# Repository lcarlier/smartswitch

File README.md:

# My Smart switch
This project implements a smart switch based on Atmega328 that has the following requirements:

- Must fit into a wall switch case box
- Must be as less invasive as possible. Which means I did not want to change anything in my electrical installation, e.g to change my regular switches to push button switches.
- The physical switch must be available and functional (you don't want your wife to be angry with you because she can't open a light without her cellphone ;) )
- Even if my smart switch is blocked or dead, the physical switch must still work

Here is the way the Smart switch is to be connected with the 3 way physical switch

For the full description of this project, please consult [this post on my website](https://www.laurentcarlier.com/2018/04/My-smart-switch-project.html).

I also have 2 videos. The first one showing the project operating a small LED without any problem. The second video shows the
project operating a regular light bulb, but with problems.

- https://youtu.be/OeRLf1SrVcU
- https://youtu.be/o9J_xXDBoP8

On the second video, the power supply (HPK-PM01) was not in used yet. The power is provided by the 5V serial connector.

I do not have any idea yet what the problem is. Do not hesitate to contact me if you have a clue of what the problem can be. I'm most likely missing something related to high voltages and noise.

Enjoy!

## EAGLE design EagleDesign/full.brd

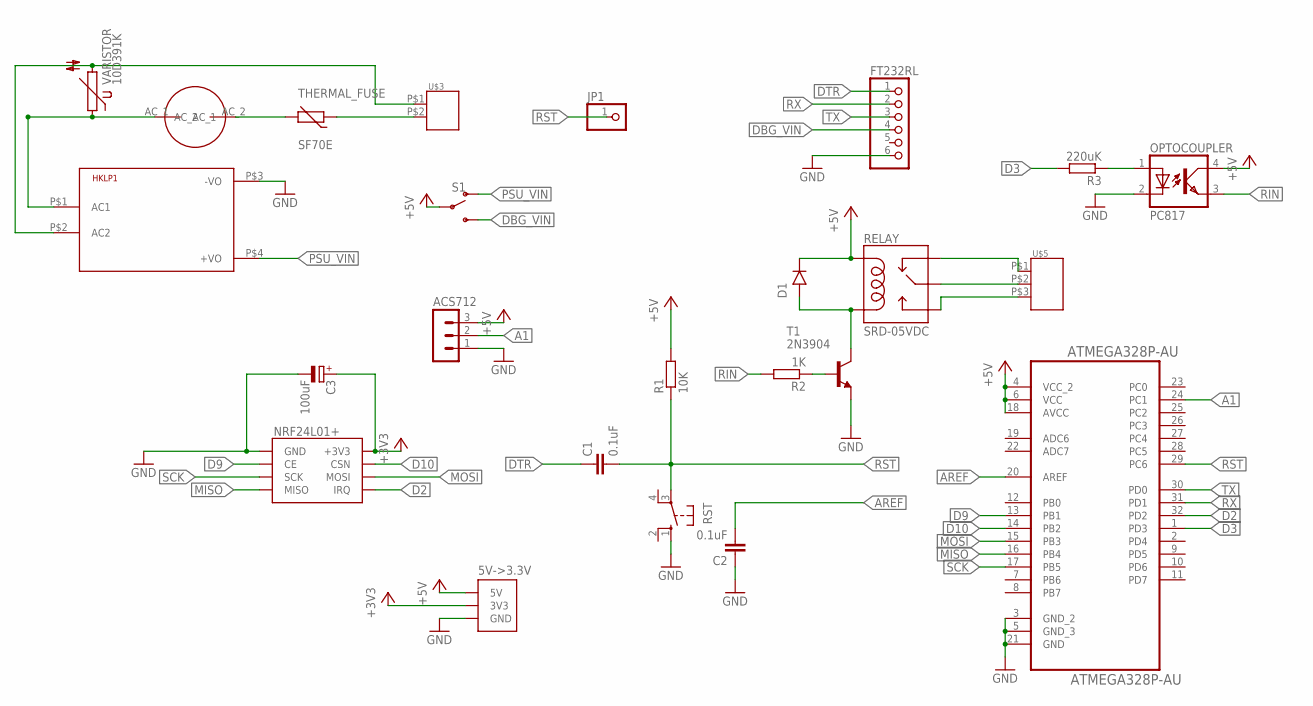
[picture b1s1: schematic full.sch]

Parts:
5V->3.3V: AMS1117_VERT
ACS712: MA03-1
ATMEGA328P-AU: ATMEGA328P-AU; QFP80P900X900X120-32N
C1, C2: 0.1uF; C050-030X075
C3: 100uF; E2,5-6
D1: 1N4001; DO41-10
FT232RL: PINHD-1X6; 1X06
FUSE: R3-24
HKLP1: HKLPM01
JP1: PINHD-1X1; 1X01
NRF24L01+: RADIO_NRF24L1; NRF24L1
OPTOCOUPLER: PC817; DIL04
R1: 10K; 0204/5
R2: 1K; 0204/5
R3: 220uK; 0204/5
RELAY: SRD-05VDC; SRD-05VDC-SL-C
RST: 10-XX; B3F-10XX
S1: SWITCH-SPDT-PTH-11.6X4.0MM; SWITCH_SPDT_PTH_11.6X4.0MM
T1: 2N3904; TO92
THERMAL_FUSE: SF70E; R-7,5
U$3: CONNECTOR_2SCREW; SCREW_2
U$5: CONNECTOR_3SCREW; SCREW_3
VARISTOR: 10D391K; S10K385

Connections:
+3V3: 5V->3.3V.3V3, C3.+, NRF24L01+.+3V3
+5V: 5V->3.3V.5V, ACS712.3, ATMEGA328P-AU.4 (VCC_2), ATMEGA328P-AU.6 (VCC), ATMEGA328P-AU.18 (AVCC), D1.C (CATHODE), OPTOCOUPLER.4 (COL), R1.2, RELAY.COIL1, S1.2
A1: ACS712.2, ATMEGA328P-AU.24 (PC1)
AC1_F: FUSE.AC_1, HKLP1.P$1 (AC1), VARISTOR.1
AC2: HKLP1.P$2 (AC2), U$3.P$1 (1), VARISTOR.2
AREF: ATMEGA328P-AU.20 (AREF), C2.2
D2: ATMEGA328P-AU.32 (PD2), NRF24L01+.IRQ
D3: ATMEGA328P-AU.1 (PD3), R3.2
D9: ATMEGA328P-AU.13 (PB1), NRF24L01+.CE
D10: ATMEGA328P-AU.14 (PB2), NRF24L01+.CSN
DBG_VIN: FT232RL.4, S1.3 (S)
DTR: C1.1, FT232RL.1
FU_IN: FUSE.AC_2, THERMAL_FUSE.2
GND: 5V->3.3V.GND, ACS712.1, ATMEGA328P-AU.3 (GND_2), ATMEGA328P-AU.5 (GND_3), ATMEGA328P-AU.21 (GND), C2.1, C3.-, FT232RL.6, HKLP1.P$3 (-VO), NRF24L01+.GND, OPTOCOUPLER.2 (C), RST.1 (S), T1.3 (E)
MISO: ATMEGA328P-AU.16 (PB4), NRF24L01+.MISO
MOSI: ATMEGA328P-AU.15 (PB3), NRF24L01+.MOSI
OPTO_IN: OPTOCOUPLER.1 (A), R3.1
PSU_VIN: HKLP1.P$4 (+VO), S1.1 (O)
RIN: OPTOCOUPLER.3 (EMIT), R2.2
RST: ATMEGA328P-AU.29 (PC6), C1.2, JP1.1, R1.1, RST.3
RX: ATMEGA328P-AU.31 (PD1), FT232RL.2
R_CENTER: RELAY.SWCOMMON, U$5.P$2 (2)
R_IN: D1.A (ANODE), RELAY.COIL0, T1.1 (C)
R_LEFT: RELAY.SWOPEN, U$5.P$3 (3)
R_RIGHT: RELAY.SWCLOSED (SWCLOSE), U$5.P$1 (1)
SCK: ATMEGA328P-AU.17 (PB5), NRF24L01+.SCK
TR_IN: THERMAL_FUSE.1, U$3.P$2 (2)
TX: ATMEGA328P-AU.30 (PD0), FT232RL.3
T_IN: R2.1, T1.2 (B)

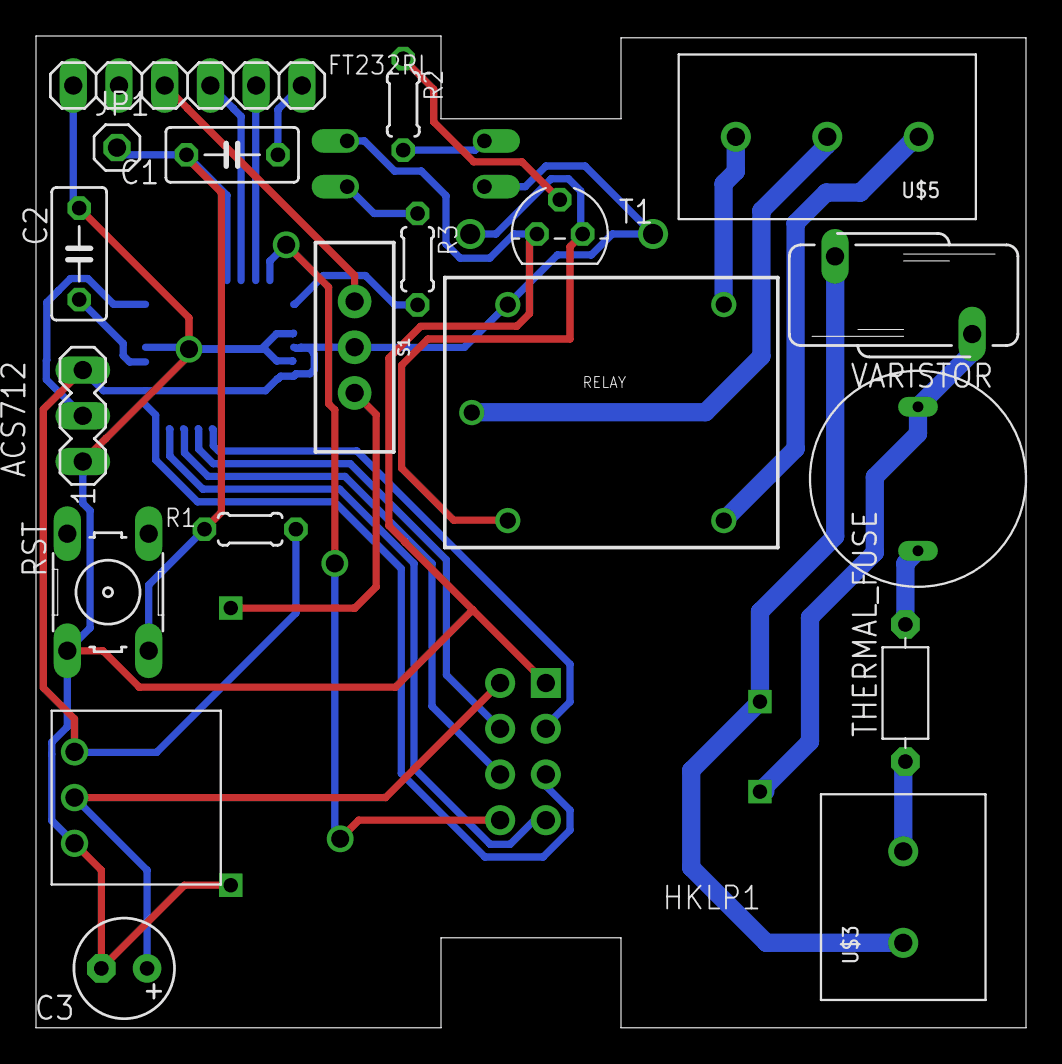
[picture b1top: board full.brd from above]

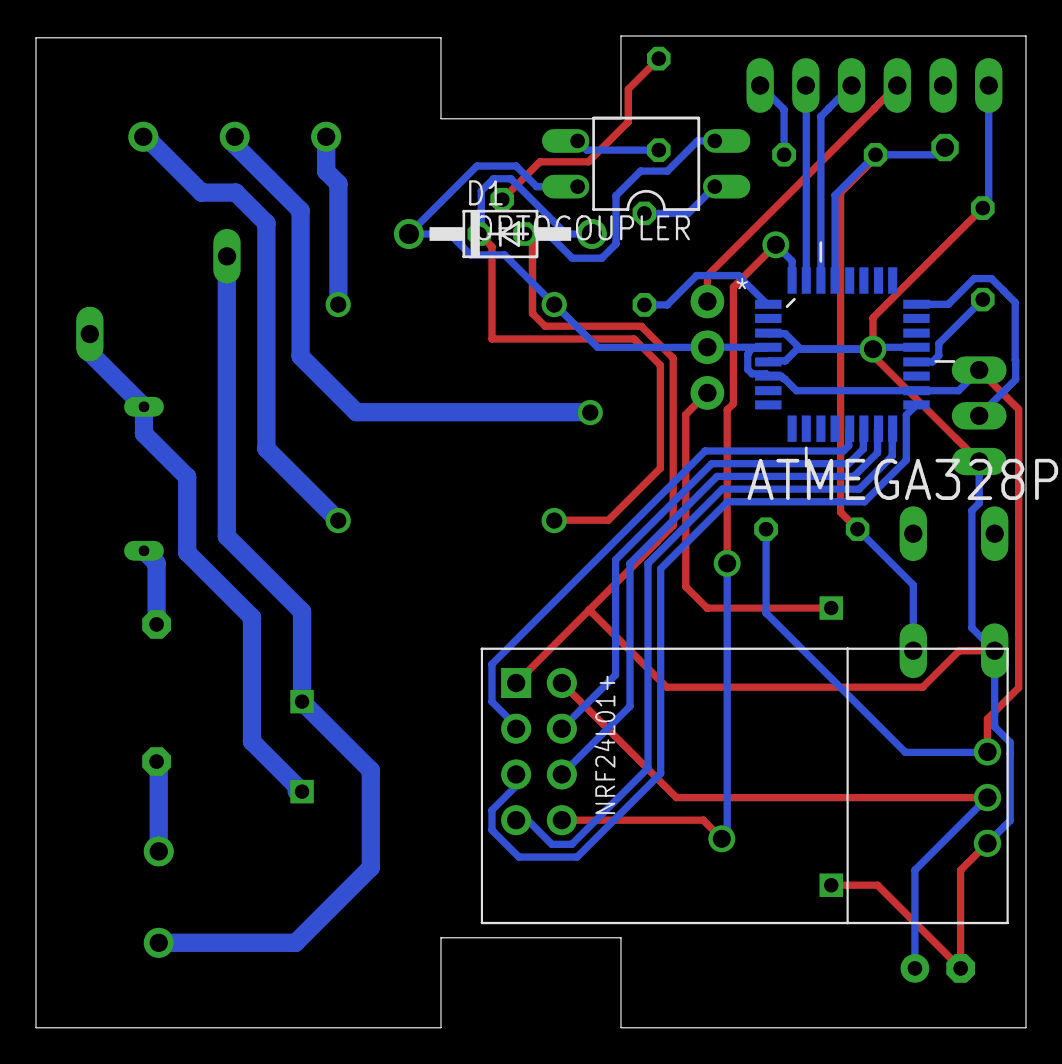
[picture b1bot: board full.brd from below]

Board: 2 copper layers, 55.0 x 55.1 mm, 24 parts (4 on the bottom side), 29 nets.

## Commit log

2018-05-11 upload V2 of design
2018-06-04 add smart switch connection
2018-06-04 remove extra text shown in readme
2018-06-04 use image version from OpenHardware.io
2018-06-09 update smart switch image
2018-06-09 rename smart switch connection to be able to update on openhardware.io
2018-06-09 update smart switch connection image on readme

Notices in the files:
parts and their libraries:
SparkFun-Switches: Licensing: Creative Commons ShareAlike 4.0 International - https://creativecommons.org/licenses/by-sa/4.0
